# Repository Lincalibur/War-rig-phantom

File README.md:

<div align="center">

# War-rig-phantom
### *A Portable OPSEC/OSINT Recon Deck*

**A full ESP32-DIV multi-tool handheld (WiFi / BLE / 2.4 GHz / sub-GHz) plus standalone recon modules, with GPS-tagged logging**

**[Build page](https://lincalibur.github.io/War-rig-phantom/)**: boards, wiring diagram, parts checklist and build order

</div>

---

## Overview

**War-rig-phantom** is a portable wireless multi-tool and recon kit made of separate modules. Each module has its own screen and job:

- **`HUB`:** a full ESP32-DIV V1 handheld on an ESP32-WROOM-32U with a router antenna and a radio shield (3× NRF24L01 + CC1101). It has a 2.4" touch TFT, buttons and a NEO-7M GPS. It runs the complete ESP32-DIV toolkit — WiFi scan/deauth/evil-portal/packet-monitor, BLE scan/spoof/jam, 2.4 GHz (NRF24) and sub-GHz (CC1101) tools, deauth detection, and GPS wardriving logged to SD as WiGLE CSV.
- **`WIFI-NODE` → `READOUT`:** an ESP32-C3 WiFi sniffer streams to an Arduino UNO with a 3.5" screen. It sorts clients by how long they've been nearby, which flags devices that keep following you.
- **`STATUS`:** a removable ESP32-C3 + OLED watch that logs GPS and WiFi scans to a phone.

The modules share one 3x 18650 pack and a 5 V boost module. Later, all the logs go to a laptop for analysis.

> **Scope & Ethics**
> The HUB runs the full ESP32-DIV firmware, which **includes active, transmitting attack tools** (deauth, beacon/probe flood, evil portal, BLE spoof/jam, NRF24 and CC1101 jam/replay).
> - Use them **only** against hardware you own and control — the project's test laptop and spare router, on an isolated bench.
> - Never transmit against networks, devices or people you don't own. Deauth and jamming are illegal in most jurisdictions when aimed at others, and the radios interfere with anyone nearby.
> - The passive recon modules (`WIFI-NODE`/`READOUT`, `STATUS`) only listen and log.
>
> This is an authorized-testing and learning platform. You are responsible for staying within the law.

## Architecture

```mermaid
flowchart TD
    subgraph HUBG["HUB · ESP32-DIV V1 firmware"]
      ESP["ESP32-WROOM-32U<br/>router antenna on U.FL"]
      TFT["2.4 in ILI9341<br/>touch + SD"]
      PCF["PCF8574<br/>5 buttons"]
      GPS["GPS · NEO-7M"]
      RADIO["Radio shield<br/>3x NRF24L01 + CC1101"]
      ESP -->|SPI| TFT
      ESP -->|I2C| PCF
      GPS -->|UART| ESP
      ESP -->|shared SPI| RADIO
    end
    WIFI["WIFI-NODE<br/>ESP32-C3, promiscuous"] -->|UART 19200| READOUT["READOUT<br/>UNO + 3.5 in TFT"]
    STATUS["STATUS · C3 + OLED watch"] -->|CSV| PHONE["Android phone"]
    TFT --> SD[("SD card<br/>WiGLE CSV, PCAP")]
    SD -.->|later| LAPTOP["Laptop analysis"]
    PHONE -.->|later| LAPTOP

    subgraph POWER["Power"]
      direction LR
      BAT["3x 18650 in parallel"] --> MSW["master switch"] --> BOOST["5V 2A charge/boost"] --> RAIL["5 V to every module"]
    end
```

Wiring for the `HUB` is on the build page and in three drawings: [`docs/wiring-overview.svg`](docs/wiring-overview.svg) (the ESP32 + touchscreen assembly and the protoboard, joined by the 6-wire J1 cable), [`docs/wiring.svg`](docs/wiring.svg) (ESP32 + touchscreen) and [`docs/wiring-protoboard.svg`](docs/wiring-protoboard.svg) (GPS, PCF8574 and buttons). Board names are defined in [`docs/hardware-layout.md`](docs/hardware-layout.md#board-names).

## Repository

| Path | What's in it |
|---|---|
| [`docs/OVERVIEW.md`](docs/OVERVIEW.md) | **Start here.** Goals, decisions, capabilities, status and next steps |
| [`docs/hardware-layout.md`](docs/hardware-layout.md) | The current build: board names, HUB pins, power, case |
| [`cad/wiring/`](cad/wiring/) | Script that draws the HUB wiring diagrams |
| [`docs/build-page.html`](docs/build-page.html) | Source of the build page (deployed by `.github/workflows/pages.yml`) |
| [`v2/`](v2/README.md) | Firmware: the working `WIFI-NODE` + `READOUT` sketches, plus shelved hub and node code |
| [`docs/proto-readout-wiring.html`](docs/proto-readout-wiring.html) | `WIFI-NODE` → `READOUT` wiring |
| [`docs/BOARD-BLE-SCAN-ESP32-1732S019.md`](docs/BOARD-BLE-SCAN-ESP32-1732S019.md) | Spec for the `BLE-SCAN` board (on hand, not in this build) |
| [`cad/case_filler/`](cad/case_filler/), [`docs/PCB-BOM-AND-NETLIST.md`](docs/PCB-BOM-AND-NETLIST.md), [`docs/esp32-hub-board.html`](docs/esp32-hub-board.html), [`KiCad Design/`](KiCad%20Design/) | Shelved designs: Pi 5 clamshell filler and single PCB |
| [`docs/debian-esp32-server-guide.md`](docs/debian-esp32-server-guide.md) | Remote compile/flash station over SSH (the server is being rebuilt) |

The `HUB` runs cifertech's [ESP32-DIV](https://github.com/cifertech/ESP32-DIV) firmware, v1 target, unmodified — flashed from the stock `ESP32-DIV-v1-v1.7.2.bin`. The radio shield's NRF24/CC1101 pins are fixed by the firmware's `shared.h`, so no source changes are needed; wire to the pins in [`docs/hardware-layout.md`](docs/hardware-layout.md#radio-shield-nrf24--cc1101).

The v1 build (ESP-NOW C3 nodes and an ESP32-1732S019 hub) was removed from the tree. Recover it with `git checkout v1-espnow-archive`.

## Status

| Area | State |
|---|---|
| HUB parts | 🟨 ordered from nde3d 2026-11-02, waiting for collection |
| HUB wiring and firmware | 🟨 wiring drawn from the firmware pins; prebuilt v1.7.0 ready to flash |
| WIFI-NODE + READOUT | ✅ working on the bench |
| STATUS watch | ✅ working |
| Power system | ⬜ ordered; bench test first |
| Case layout | ⬜ to be redrawn for these parts |
| Laptop analysis | ⬜ planned |

## License

See [LICENSE](LICENSE).

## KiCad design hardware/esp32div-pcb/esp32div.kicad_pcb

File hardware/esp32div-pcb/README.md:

# ESP32-DIV HUB — KiCad carrier PCB (schematic pre-built)

A starting point for routing a custom carrier/shield PCB for the **HUB** board
(the ESP32-DIV handheld in [`../../docs/hardware-layout.md`](../../docs/hardware-layout.md)).
Every plug-in module is a female-header footprint; the ESP32 dev board and all
modules socket in. This does **not** change the design — it just captures the
existing HUB pinout in KiCad so you can place and route.

Built and validated against **KiCad 10.0.6**. Netlist checked pin-by-pin; ERC
clean except one benign warning (see below).

## Files
| File | What it is |
|---|---|
| `esp32div.kicad_sch` | The schematic: 39 symbols, all nets labelled, ready for PCB. |
| `esp32div.kicad_pro` | Project file. Includes a **Power** netclass (1 mm tracks) auto-applied to `+5V`, `+3V3`, `GND`, `VBAT`, `VBOOST`. |
| `generate_schematic.py` | The generator. Edit the pin maps and re-run (`python generate_schematic.py .`) to regenerate the schematic. |

## Go straight to routing
1. Open `esp32div.kicad_pro` in KiCad.
2. Open the **PCB Editor** (it creates `esp32div.kicad_pcb`).
3. **Tools → Update PCB from Schematic** (F8) → *Update*. All 39 footprints drop
   in with the full ratsnest.
4. Draw a board outline on Edge.Cuts, then place and route. The power nets are
   already on 1 mm tracks via the Power netclass.

## The one ERC warning
`lib_symbol_mismatch` on `PCF8574T` — the PCF8574 is a *derived* library symbol,
so the cached copy isn't byte-identical to the library. It's cosmetic and does
**not** affect the netlist or PCB. To clear it: **Tools → Update Symbols from
Library** in the schematic editor.

## ⚠️ Verify before you fab (modelled from docs, not physical parts)
- **ESP32 pin order (most important).** `J1`/`J2` are modelled as two 1×19
  headers using the standard **38-pin DevKitC-V4** order. Confirm against your
  actual WROOM-32U board when it arrives. If a pin differs, just drag the net
  label to the correct pin (or edit the pin map in `generate_schematic.py` and
  re-run). The board can't be finalised until the dev-board variant is confirmed
  (see the open question in `hardware-layout.md`).
- **TFT header (`J3`).** Modelled as one 18-way header with the full
  TFT+touch+SD signal set. Match pin order/count to your physical 2.4" module.
- **CC1101 (`J8`) and NRF24 (`J5–J7`) pin order.** Vendor-dependent; check the
  silkscreen on your modules. NRF24 uses a 2×4 socket footprint.
- **VCC rails.** TFT and GPS VCC are on `+5V` per the docs (both have on-board
  regulators). Confirm your modules accept 5 V. PCF8574, NRF24, CC1101 are on
  `+3V3`.

## Design notes carried over from the docs
- Two SPI buses: display pixels on `TFT_*` (IO14/13/12), everything else (touch,
  SD, 3× NRF24, CC1101) on the shared `SH_*` bus (IO18/23/19).
- Intentionally **shared** control nets (cifertech firmware time-shares them):
  `SD_CS_NRF1_CSN` (IO5), `NRF2_CE_CC_GDO0` (IO26), `NRF2_CSN_CC_CS` (IO27),
  `NRF3_CE_CC_GDO2` (IO16). These fan out to several module pins by design.
- Decoupling: 100 nF at every module VCC; extra 10 µF at each NRF24, the CC1101
  and the GPS. Keep them at the pins when you place.
- Consider the optional separate 3V3 LDO for the radios (not placed) if the dev
  board's regulator browns out under 3× NRF24 + CC1101.

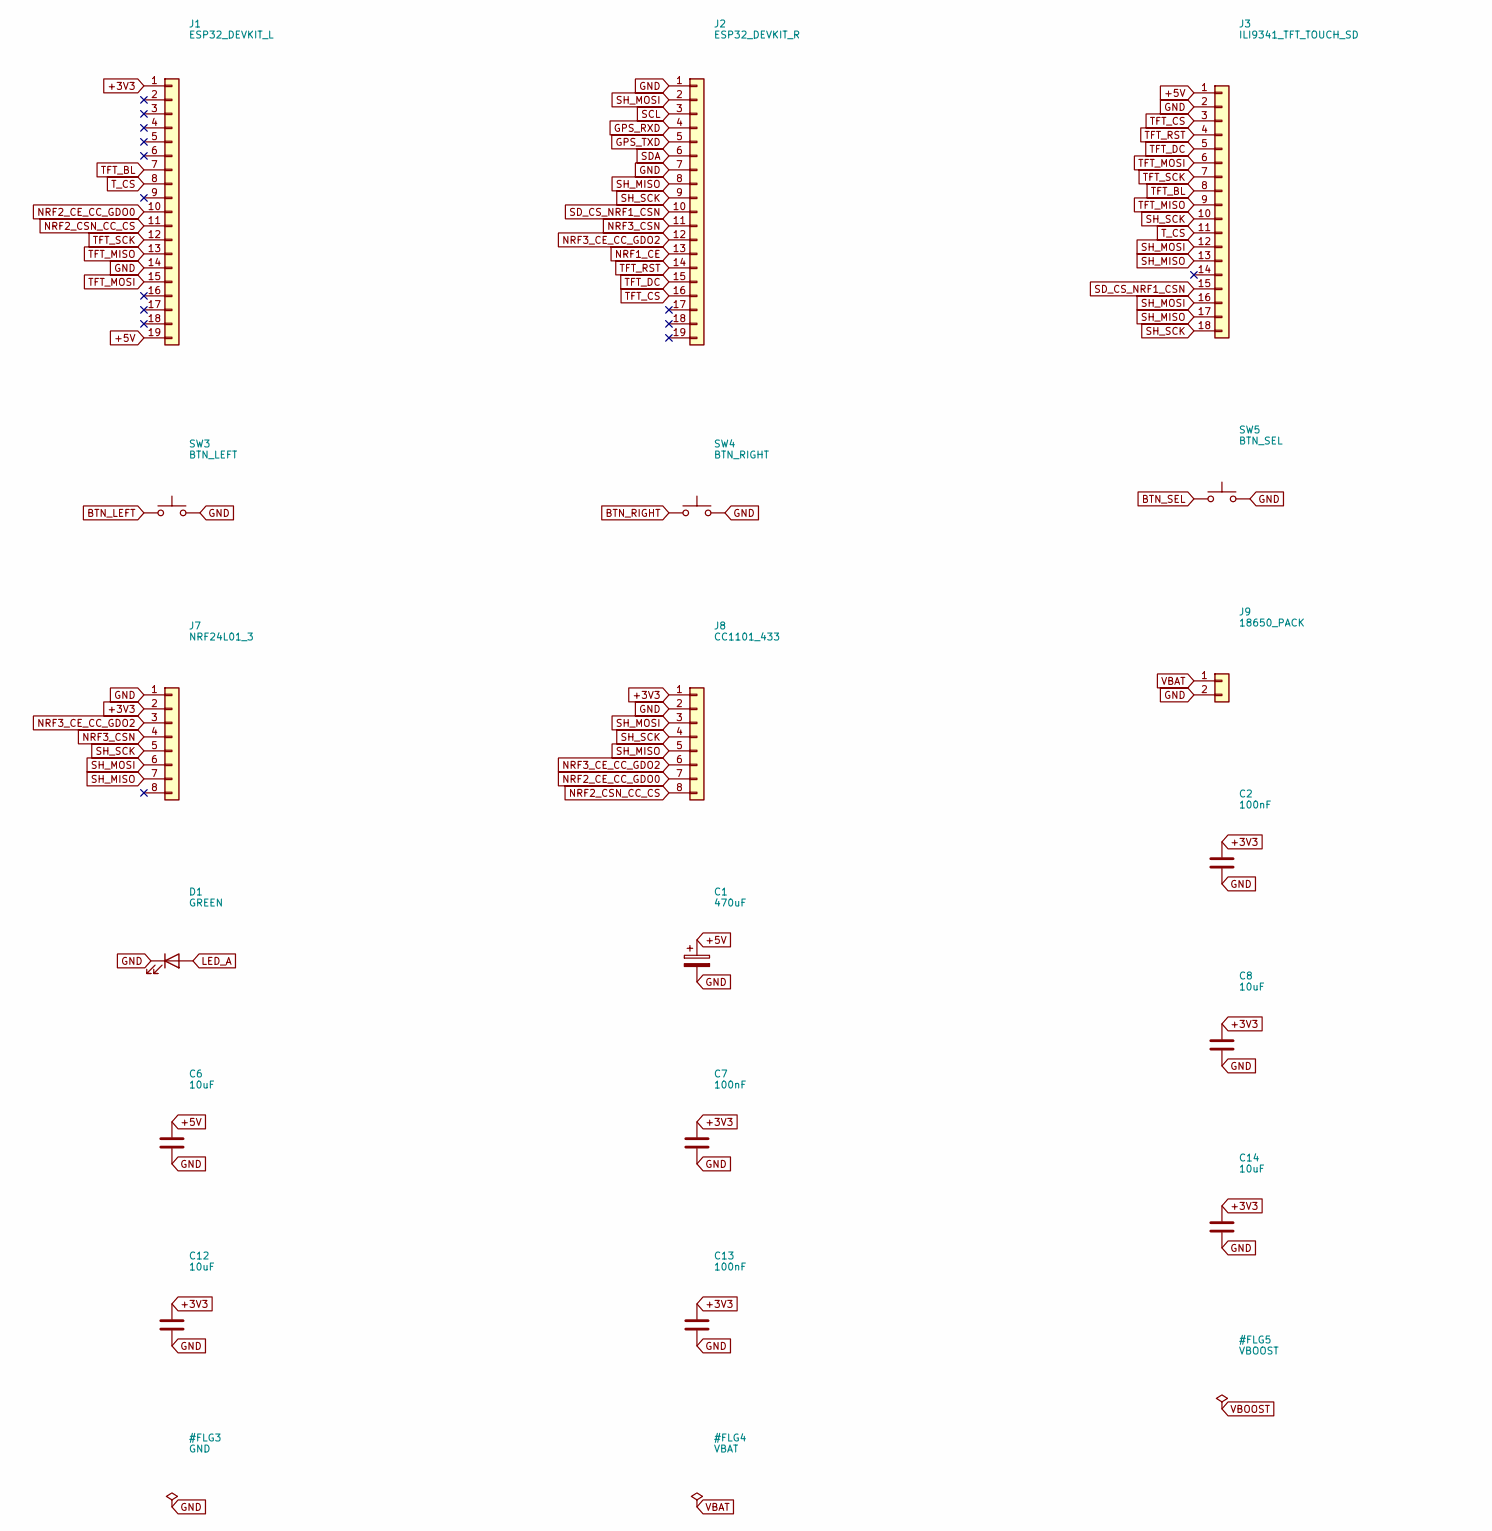
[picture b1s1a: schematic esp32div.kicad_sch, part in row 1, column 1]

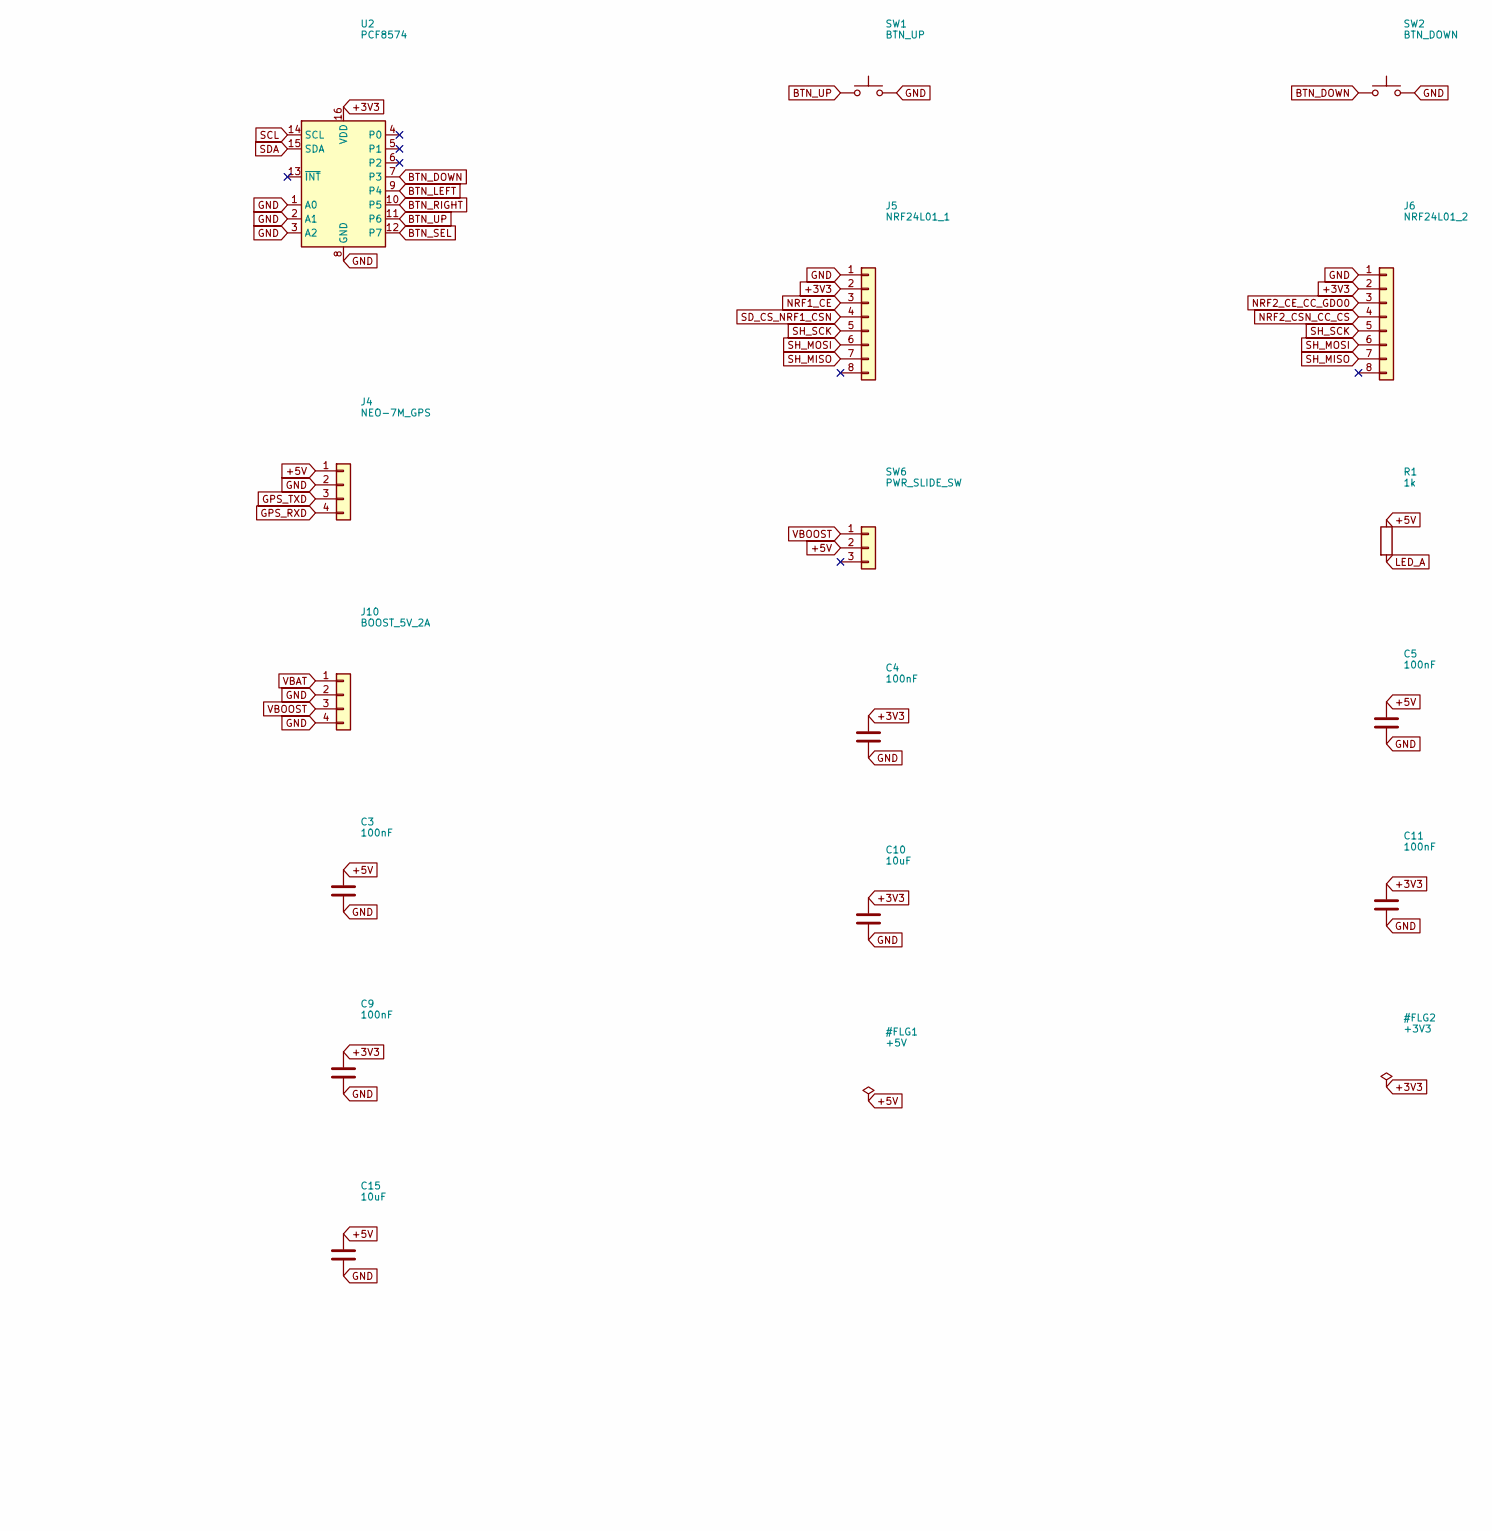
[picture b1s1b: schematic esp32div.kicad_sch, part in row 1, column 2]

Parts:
C1: 470uF; CP_Radial_D8.0mm_P3.50mm
C2, C3, C4, C5, C7, C9, C11, C13: 100nF; C_Disc_D5.0mm_W2.5mm_P5.00mm
C6, C8, C10, C12, C14, C15: 10uF; CP_Radial_D5.0mm_P2.50mm
D1: GREEN; LED_D3.0mm
J1: ESP32_DEVKIT_L; PinSocket_1x19_P2.54mm_Vertical
J2: ESP32_DEVKIT_R; PinSocket_1x19_P2.54mm_Vertical
J3: ILI9341_TFT_TOUCH_SD; PinSocket_1x18_P2.54mm_Vertical
J4: NEO-7M_GPS; PinSocket_1x04_P2.54mm_Vertical
J5: NRF24L01_1; PinSocket_2x04_P2.54mm_Vertical
J6: NRF24L01_2; PinSocket_2x04_P2.54mm_Vertical
J7: NRF24L01_3; PinSocket_2x04_P2.54mm_Vertical
J8: CC1101_433; PinSocket_1x08_P2.54mm_Vertical
J9: 18650_PACK; PinHeader_1x02_P2.54mm_Vertical
J10: BOOST_5V_2A; PinHeader_1x04_P2.54mm_Vertical
R1: 1k; R_Axial_DIN0207_L6.3mm_D2.5mm_P7.62mm_Horizontal
SW1: BTN_UP; SW_PUSH_6mm
SW2: BTN_DOWN; SW_PUSH_6mm
SW3: BTN_LEFT; SW_PUSH_6mm
SW4: BTN_RIGHT; SW_PUSH_6mm
SW5: BTN_SEL; SW_PUSH_6mm
SW6: PWR_SLIDE_SW; PinHeader_1x03_P2.54mm_Vertical
U2: PCF8574; SOIC-16_3.9x9.9mm_P1.27mm

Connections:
+3V3: C2.1, C4.1, C7.1, C8.1, C9.1, C10.1, C11.1, C12.1, C13.1, C14.1, J1.1, J5.2, J6.2, J7.2, J8.1, U2.16 (VDD)
+5V: C1.1, C3.1, C5.1, C6.1, C15.1, J1.19, J3.1, J4.1, R1.1, SW6.2
BTN_DOWN: SW2.1, U2.7 (P3)
BTN_LEFT: SW3.1, U2.9 (P4)
BTN_RIGHT: SW4.1, U2.10 (P5)
BTN_SEL: SW5.1, U2.12 (P7)
BTN_UP: SW1.1, U2.11 (P6)
GND: C1.2, C2.2, C3.2, C4.2, C5.2, C6.2, C7.2, C8.2, C9.2, C10.2, C11.2, C12.2, C13.2, C14.2, C15.2, D1.1 (K), J1.14, J2.1, J2.7, J3.2, J4.2, J5.1, J6.1, J7.1, J8.2, J9.2, J10.2, J10.4, SW1.2, SW2.2, SW3.2, SW4.2, SW5.2, U2.1 (A0), U2.2 (A1), U2.3 (A2), U2.8 (GND)
GPS_RXD: J2.4, J4.4
GPS_TXD: J2.5, J4.3
LED_A: D1.2 (A), R1.2
NRF1_CE: J2.13, J5.3
NRF2_CE_CC_GDO0: J1.10, J6.3, J8.7
NRF2_CSN_CC_CS: J1.11, J6.4, J8.8
NRF3_CE_CC_GDO2: J2.12, J7.3, J8.6
NRF3_CSN: J2.11, J7.4
SCL: J2.3, U2.14 (SCL)
SDA: J2.6, U2.15 (SDA)
SD_CS_NRF1_CSN: J2.10, J3.15, J5.4
SH_MISO: J2.8, J3.13, J3.17, J5.7, J6.7, J7.7, J8.5
SH_MOSI: J2.2, J3.12, J3.16, J5.6, J6.6, J7.6, J8.3
SH_SCK: J2.9, J3.10, J3.18, J5.5, J6.5, J7.5, J8.4
TFT_BL: J1.7, J3.8
TFT_CS: J2.16, J3.3
TFT_DC: J2.15, J3.5
TFT_MISO: J1.13, J3.9
TFT_MOSI: J1.15, J3.6
TFT_RST: J2.14, J3.4
TFT_SCK: J1.12, J3.7
T_CS: J1.8, J3.11
VBAT: J9.1, J10.1
VBOOST: J10.3, SW6.1

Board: 2 copper layers, 34 parts (28 on the bottom side), 32 nets, no tracks yet.

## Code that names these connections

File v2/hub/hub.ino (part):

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// Pins
// ---------------------------------------------------------------------------------------
static const int PIN_SCLK = 12, PIN_MOSI = 11, PIN_MISO = 13;
static const int PIN_TFT_CS = 10, PIN_TFT_DC = 9, PIN_TFT_RST = 8, PIN_TFT_BL = 7;
static const int PIN_SD_CS = 14;
static const int PIN_CC1101_CS = 15;   // reserved; held high so it doesn't fight the shared bus
static const int PIN_WIFI_RX = 4, PIN_WIFI_TX = 5;   // UART1 <-> WiFi node
static const int PIN_BLE_RX  = 1, PIN_BLE_TX  = 2;   // UART2 <-> BLE node
static const int PIN_BTN_UP = 38, PIN_BTN_DOWN = 39, PIN_BTN_LEFT = 40, PIN_BTN_RIGHT = 41, PIN_BTN_SEL = 42;
static const int PIN_BAT_LOW = 47;     // PowerBoost LBO, active low

// ---------------------------------------------------------------------------------------
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// Display
// ---------------------------------------------------------------------------------------
static SPIClass hubSpi(FSPI);
static Adafruit_ILI9341 tft(&hubSpi, PIN_TFT_DC, PIN_TFT_CS, PIN_TFT_RST);

static const uint16_t C_BG = 0x0000, C_FG = 0xFFFF, C_GRAY = 0x8410, C_GREEN = 0x07E0, C_RED = 0xF800,
                      C_YELLOW = 0xFFE0, C_CYAN = 0x07FF, C_ORANGE = 0xFD20, C_HEAD = 0x0010;
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// ---------------------------------------------------------------------------------------
struct Button { int pin; bool repeat; uint32_t nextMs; bool wasDown; };
static Button buttons[] = {
  {PIN_BTN_UP, true, 0, false}, {PIN_BTN_DOWN, true, 0, false}, {PIN_BTN_LEFT, false, 0, false},
  {PIN_BTN_RIGHT, false, 0, false}, {PIN_BTN_SEL, false, 0, false},
};

static void onButton(int pin) {
  if (pin == PIN_BTN_UP) scroll -= 1;
  else if (pin == PIN_BTN_DOWN) scroll += 1;
  else if (pin == PIN_BTN_LEFT) { changePage(-1); return; }
  else if (pin == PIN_BTN_RIGHT) { changePage(+1); return; }
  else if (pin == PIN_BTN_SEL) sortMode = (sortMode + 1) % SORT_COUNT;
  if (scroll < 0) scroll = 0;
  dirty = true;
}
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  Serial.begin(115200);

  // Deselect every SPI device before the bus is used.
  for (int cs : {PIN_TFT_CS, PIN_SD_CS, PIN_CC1101_CS}) { pinMode(cs, OUTPUT); digitalWrite(cs, HIGH); }
  pinMode(PIN_TFT_BL, OUTPUT); digitalWrite(PIN_TFT_BL, HIGH);
  for (Button& b : buttons) pinMode(b.pin, INPUT_PULLUP);
  pinMode(PIN_BAT_LOW, INPUT_PULLUP);

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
